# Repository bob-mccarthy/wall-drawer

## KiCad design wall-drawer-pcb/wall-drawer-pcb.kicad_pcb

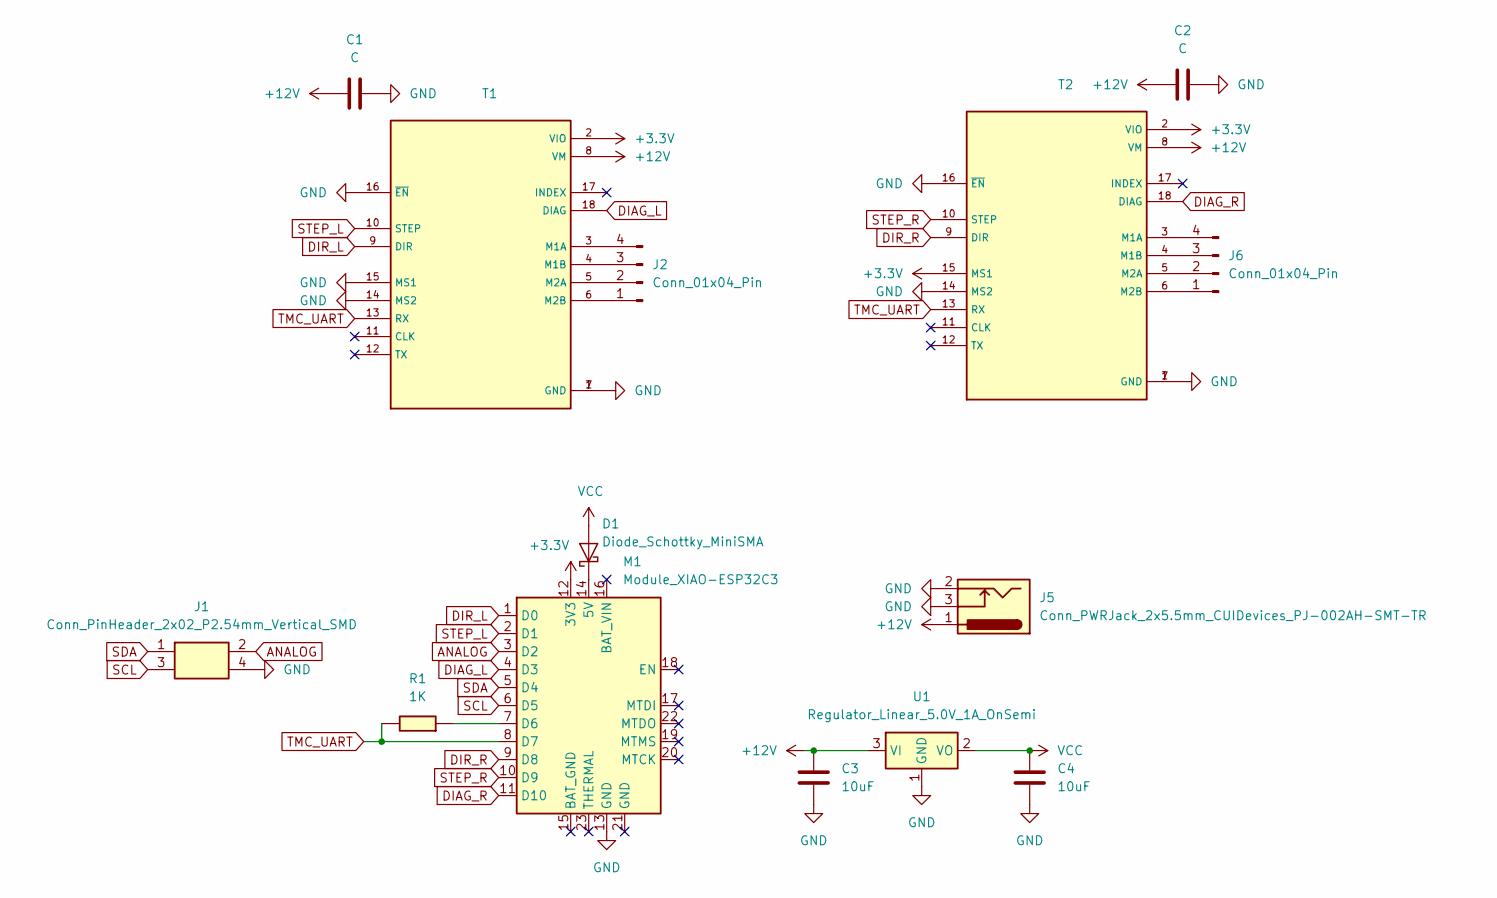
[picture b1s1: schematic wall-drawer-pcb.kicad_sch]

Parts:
C1, C2: C; CP_Radial_Tantal_D6.0mm_P2.50mm
C3, C4: 10uF; C_1206
D1: Diode_Schottky_MiniSMA
J1: Conn_PinHeader_2x02_P2.54mm_Vertical_SMD; PinHeader_2x02_P2.54mm_Vertical_SMD
J2, J6: Conn_01x04_Pin; PinHeader_1x04_P2.54mm_Vertical
J5: Conn_PWRJack_2x5.5mm_CUIDevices_PJ-002AH-SMT-TR; CUIDevices_PJ-002AH-SMT-TR_PWRJack_2x5.5mm
M1: Module_XIAO-ESP32C3; SeeedStudio_XIAO_ESP32C3
R1: 1K; R_1206
T1, T2: MODULE_TMC2209_SILENTSTEPSTICK
U1: Regulator_Linear_5.0V_1A_OnSemi; SOT-223-3_TabPin2

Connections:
+3.3V: M1.12 (3V3), T1.2 (VIO), T2.2 (VIO), T2.15 (MS1)
+12V: C1.1, C2.1, C3.1, J5.1, T1.8 (VM), T2.8 (VM), U1.3 (VI)
ANALOG: J1.2, M1.3 (D2)
DIAG_L: M1.4 (D3), T1.18 (DIAG)
DIAG_R: M1.11 (D10), T2.18 (DIAG)
DIR_L: M1.1 (D0), T1.9 (DIR)
DIR_R: M1.9 (D8), T2.9 (DIR)
GND: C1.2, C2.2, C3.2, C4.2, J1.4, J5.2, J5.3, M1.13 (GND), T1.1 (GND), T1.7 (GND), T1.14 (MS2), T1.15 (MS1), T1.16 (~EN), T2.1 (GND), T2.7 (GND), T2.14 (MS2), T2.16 (~EN), U1.1 (GND)
unnamed: D1.1 (K), M1.14 (5V)
unnamed: J2.1, T1.6 (M2B)
unnamed: J2.2, T1.5 (M2A)
unnamed: J2.3, T1.4 (M1B)
unnamed: J2.4, T1.3 (M1A)
unnamed: J6.1, T2.6 (M2B)
unnamed: J6.2, T2.5 (M2A)
unnamed: J6.3, T2.4 (M1B)
unnamed: J6.4, T2.3 (M1A)
unnamed: M1.7 (D6), R1.2
SCL: J1.3, M1.6 (D5)
SDA: J1.1, M1.5 (D4)
STEP_L: M1.2 (D1), T1.10 (STEP)
STEP_R: M1.10 (D9), T2.10 (STEP)
TMC_UART: M1.8 (D7), R1.1, T1.13 (RX), T2.13 (RX)
VCC: C4.1, D1.2 (A), U1.2 (VO)

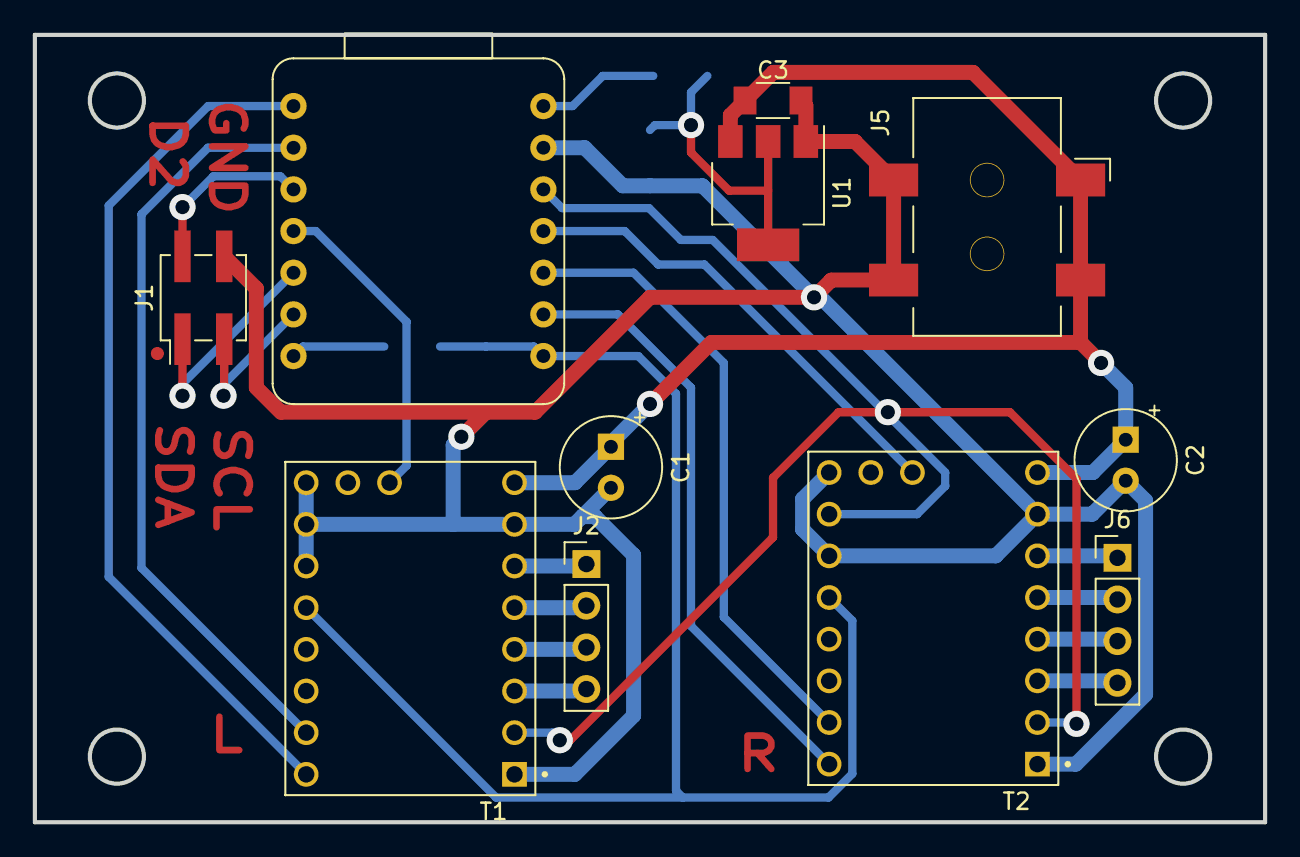
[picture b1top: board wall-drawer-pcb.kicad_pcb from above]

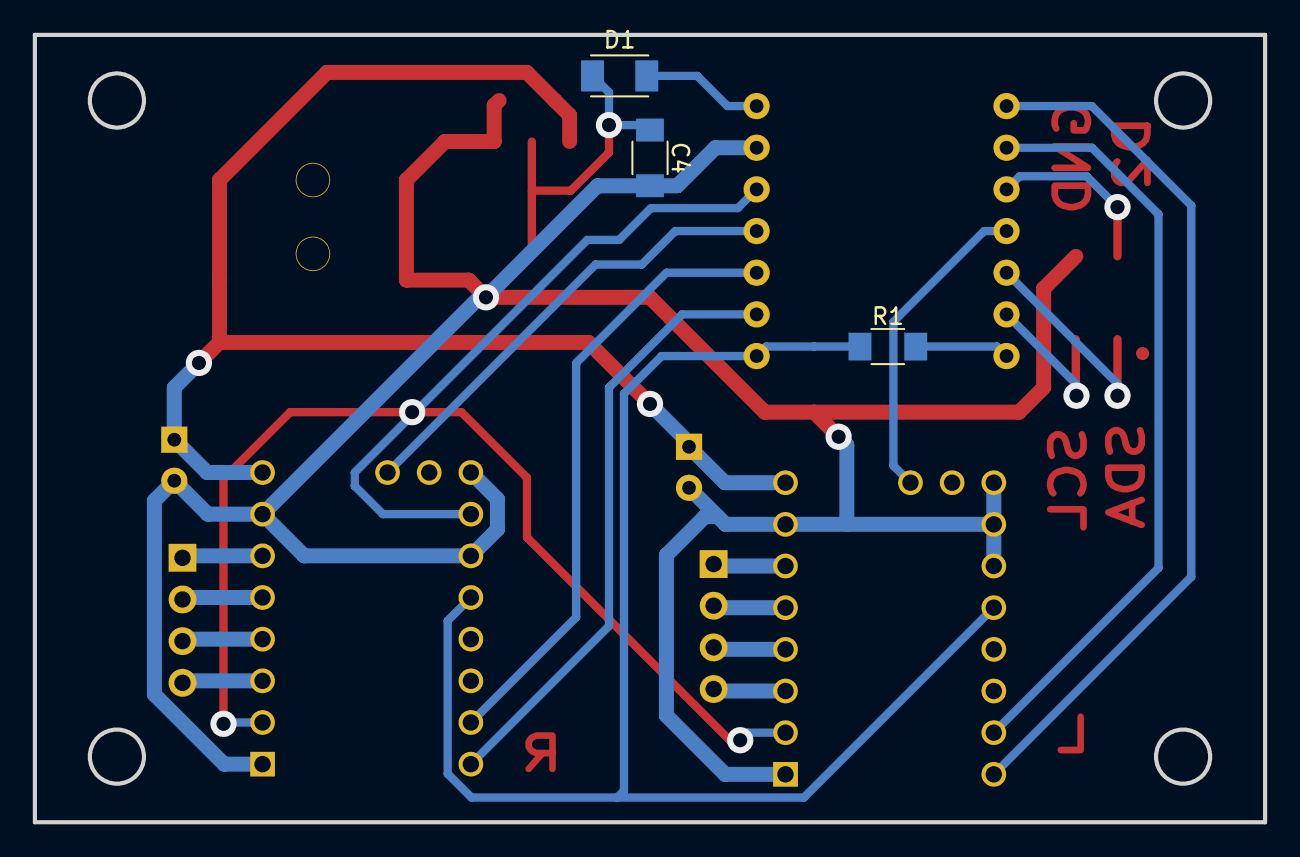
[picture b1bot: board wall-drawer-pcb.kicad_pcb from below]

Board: 2 copper layers, 75.0 x 48.0 mm, 14 parts (3 on the bottom side), 24 nets.

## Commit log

2025-06-11 init repo
2025-07-26 a4988 pcbs + simple web server
2025-07-27 wall drawer pcb to use tmc2209s
